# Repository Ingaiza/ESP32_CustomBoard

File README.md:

# Custom ESP32-C3 Development Board

## Overview
This repository contains the KiCad PCB design files for a custom development board powered by the ESP32-C3 microcontroller. This board integrates essential environmental sensing, audio input, and power management features. It serves as a robust hardware foundation for developing advanced embedded systems and IoT devices.

## Hardware Features

* **Microcontroller**: Powered by the ESP32-C3-WROOM-02-H4 module, offering Wi-Fi and Bluetooth LE connectivity.
* **Power Management**: 
    * Modern USB-C connector interface.
    * Onboard 3.3V voltage regulation via the LM1117MPX-3.3 LDO.
    * Integrated LiPo battery charging circuit utilizing the MCP73871 IC.
* **USB-to-UART Interface**: Features the CP2102N bridge for reliable serial communication and seamless flashing.
* **Memory & Storage**:
    * External 32Mb (4MB) W25Q32JVSSIQ Flash memory.
    * Dedicated MicroSD card circuit for extensive data logging.
* **Integrated Sensors**:
    * **BME280**: Environmental sensor for capturing temperature, humidity, and barometric pressure data.
    * **TEMT6000**: Ambient light sensor for environmental illumination tracking.
    * **Audio**: Electret microphone (CMC-5042PF-AC) paired with a MAX4466EXK operational amplifier for high-quality audio input.
* **User Interface & Expansion**:
    * Auto-program circuitry equipped with standard Boot and Reset tactile buttons.
    * Dedicated I2C connector optimized for OLED displays.
    * Accessible remaining GPIO breakout headers for rapid prototyping.

## Visuals & Documentation

### Top View

### Bottom View Routing

### Schematic
The complete circuit design can be viewed here: [Schematic PDF](media/Shematic.pdf)

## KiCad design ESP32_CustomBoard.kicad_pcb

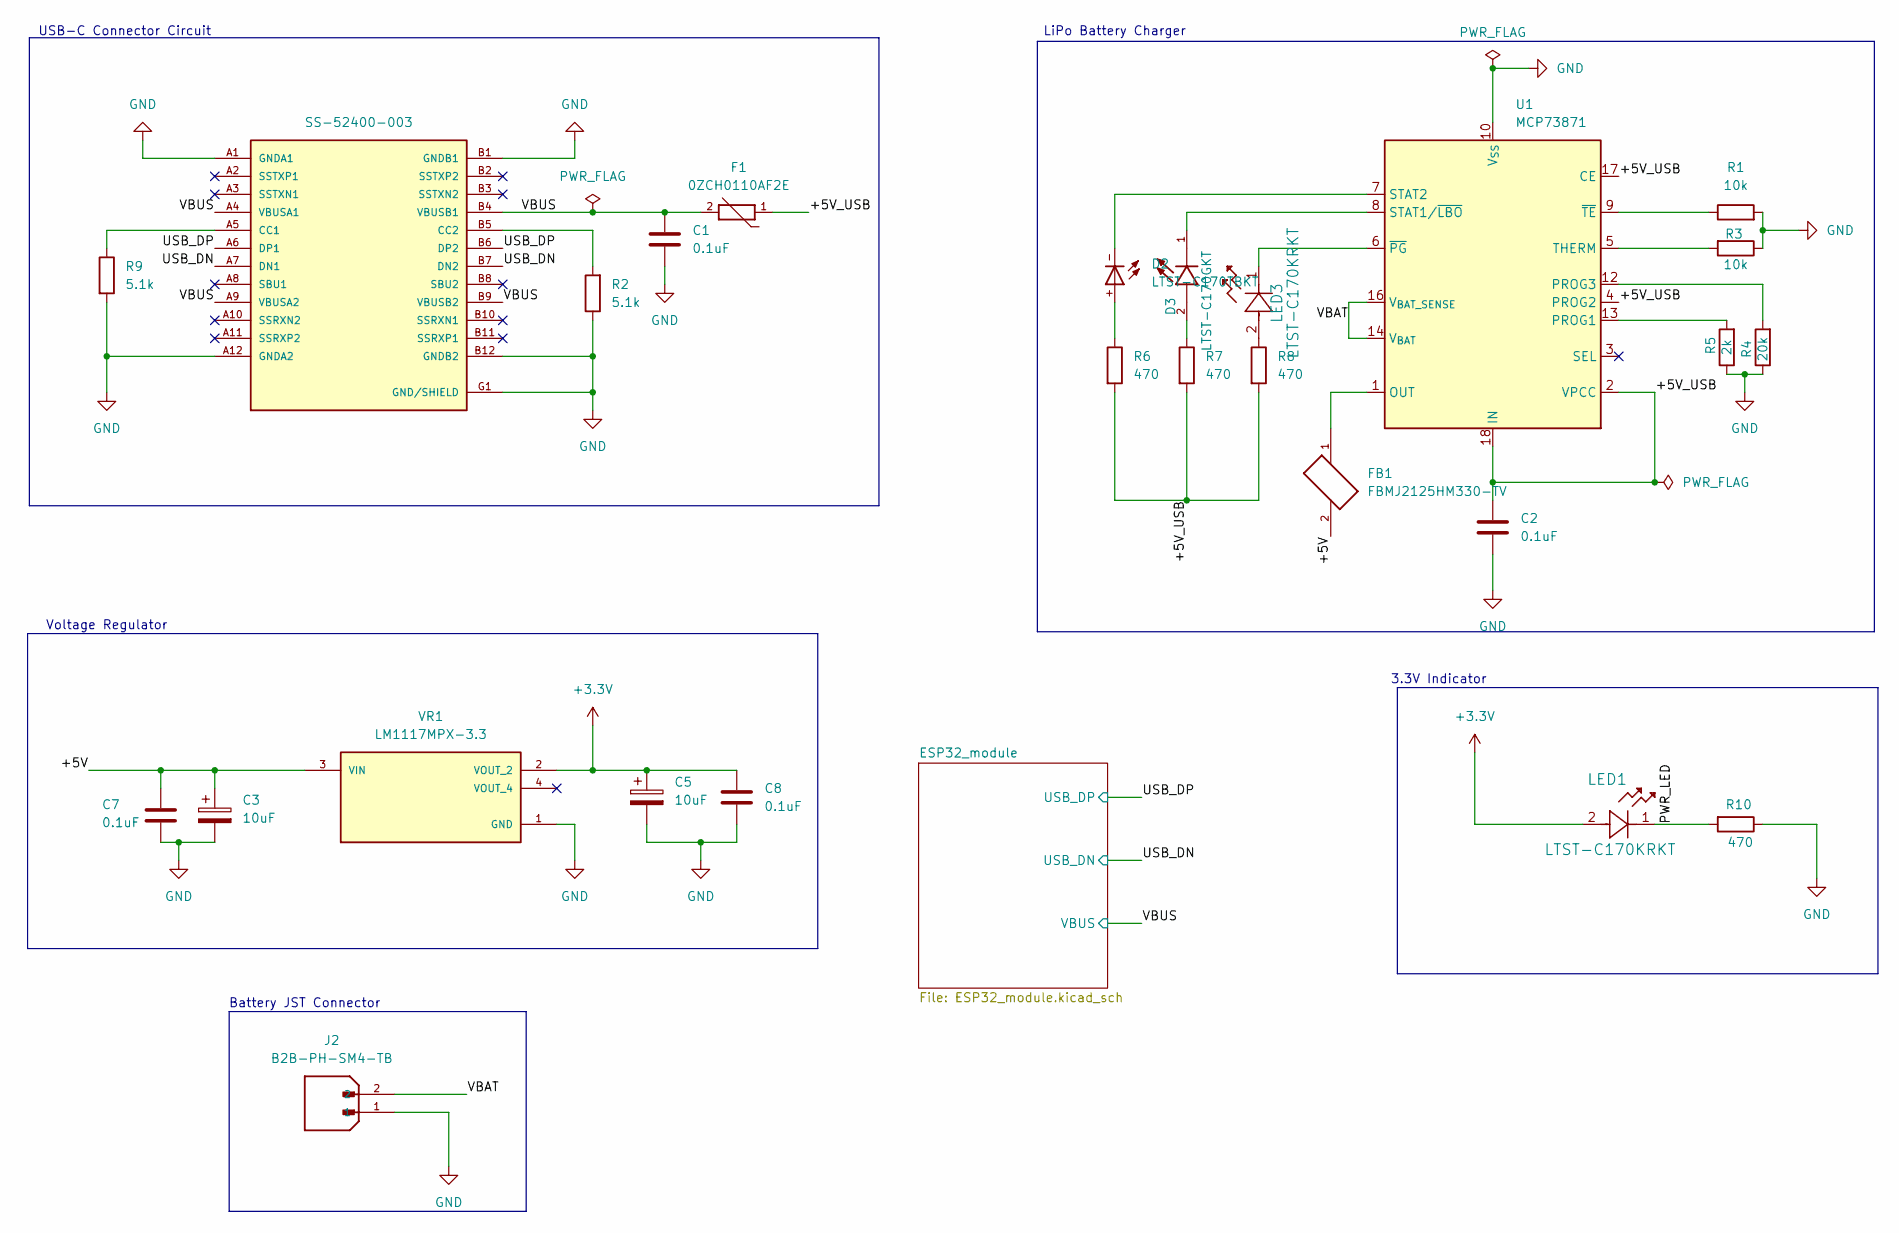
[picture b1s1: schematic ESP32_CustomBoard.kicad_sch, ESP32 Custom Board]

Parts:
C1, C2, C7, C8: 0.1uF; C_0805_2012Metric
C3, C5: 10uF; RESC3216X125N
D2: LTST-C170TBKT; DIOC200X125X110
D3: LTST-C170GKT; LED_LTST-C170GKT; PARTREV I
F1: 0ZCH0110AF2E; FUSC3225X100N; PARTREV Apr2023
FB1: FBMJ2125HM330-TV; BEADC2012X105N
J1: SS-52400-003; BELFUSE_SS-52400-003; PARTREV A0
J2: B2B-PH-SM4-TB; JST_B2B-PH-SM4-TB; PARTREV N/A
LED1, LED3: LTST-C170KRKT; LED_LTST-C170KRKT_LTO
R1, R3: 10k; R_0805_2012Metric
R2, R9: 5.1k; R_0805_2012Metric
R4: 20k; R_0805_2012Metric
R5: 2k; R_0805_2012Metric
R6, R7, R8, R10: 470; R_0805_2012Metric
U1: MCP73871; QFN-20-1EP_4x4mm_P0.5mm_EP2.5x2.5mm
VR1: LM1117MPX-3.3; VREG_LM1117MPX-3.3; PARTREV O

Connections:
+3.3V: C5.1, C8.1, LED1.2, VR1.2 (VOUT_2); also elsewhere on the board
/+5V: C3.1, C7.1, FB1.2, VR1.3 (VIN)
/+5V_USB: C2.1, F1.1, R6.2, R7.2, R8.2, U1.2 (VPCC), U1.4 (PROG2), U1.17 (CE), U1.18 (IN), U1.19 (IN)
/PWR_LED: LED1.1, R10.2
/USB_DN: J1.A7 (DN1), J1.B7 (DN2); also elsewhere on the board
/USB_DP: J1.A6 (DP1), J1.B6 (DP2); also elsewhere on the board
/VBAT: J2.2, U1.14 (V_{BAT}), U1.15 (V_{BAT}), U1.16 (V_{BAT_SENSE})
/VBUS: C1.1, F1.2, J1.A4 (VBUSA1), J1.A9 (VBUSA2), J1.B4 (VBUSB1), J1.B9 (VBUSB2); also elsewhere on the board
GND: C1.2, C2.2, C3.2, C5.2, C7.2, C8.2, J1.A1 (GNDA1), J1.A12 (GNDA2), J1.B1 (GNDB1), J1.B12 (GNDB2), J1.G1 (GND/SHIELD), J1.G2 (GND/SHIELD), J1.G3 (GND/SHIELD), J1.G4 (GND/SHIELD), J1.S1 (GND/SHIELD), J1.S2 (GND/SHIELD), J1.S3 (GND/SHIELD), J1.S4 (GND/SHIELD), J2.1, R1.2, R2.1, R3.1, R4.1, R5.1, R9.2, R10.1, U1.10 (V_{SS}), U1.11 (V_{SS}), U1.21 (V_{SS}), VR1.1 (GND); also elsewhere on the board
unnamed: D2.+, R6.1
unnamed: D3.2, R7.1
unnamed: FB1.1, U1.1 (OUT), U1.20 (OUT)
unnamed: J1.A5 (CC1), R9.1
unnamed: J1.B5 (CC2), R2.2
unnamed: LED3.2, R8.1
unnamed: R5.2, U1.13 (PROG1)
unnamed: R4.2, U1.12 (PROG3)
unnamed: D3.1, U1.8 (STAT1/~LBO)
unnamed: D2.-, U1.7 (STAT2)
unnamed: R3.2, U1.5 (THERM)
unnamed: LED3.1, U1.6 (~PG)
unnamed: R1.1, U1.9 (~TE)

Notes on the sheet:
USB-C Connector Circuit
Voltage Regulator
LiPo Battery Charger
Battery JST Connector
3.3V Indicator

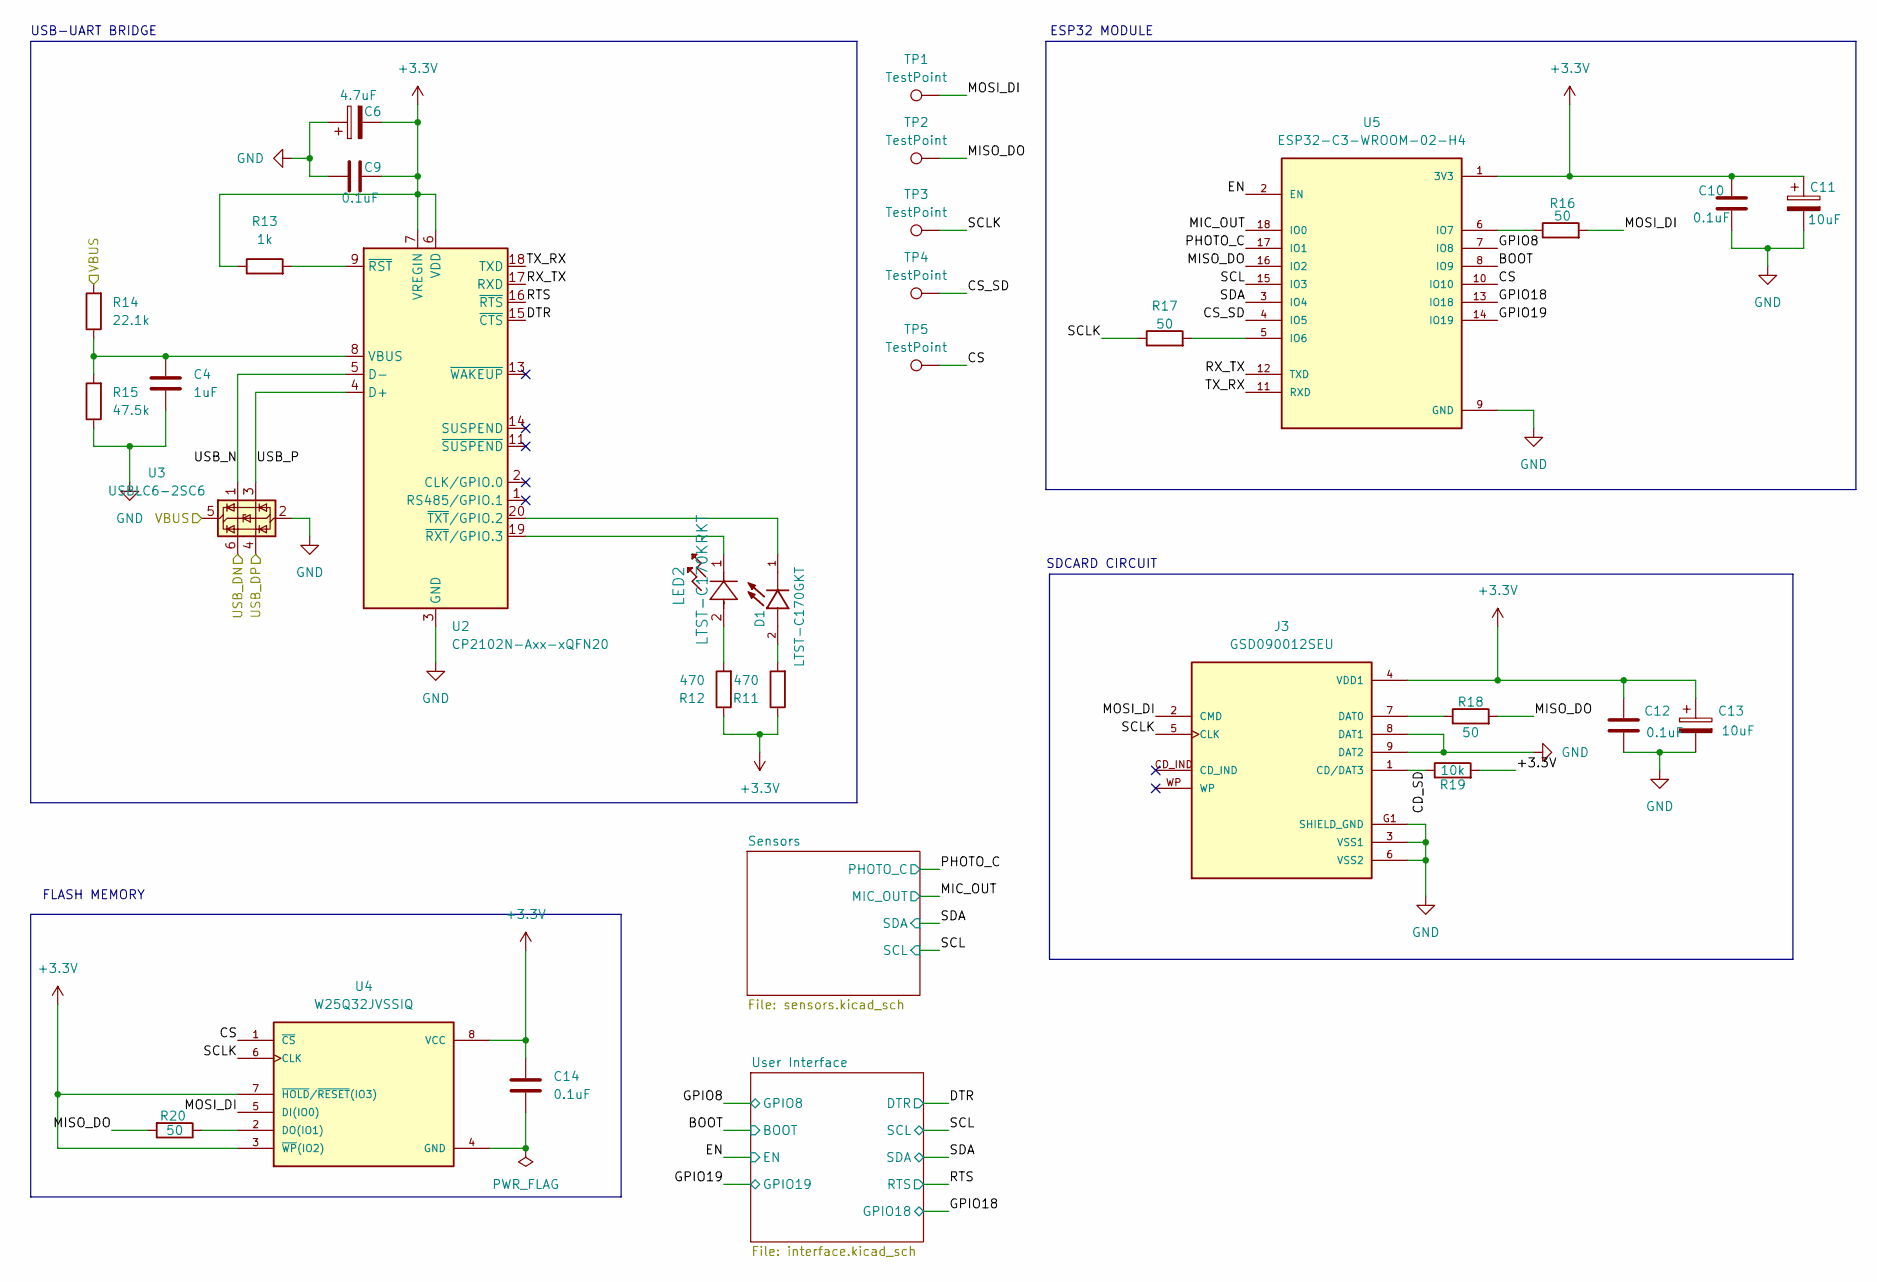
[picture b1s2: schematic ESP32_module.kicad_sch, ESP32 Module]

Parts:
C4: 1uF; C_0805_2012Metric
C6: 4.7uF; RESC3216X125N
C9, C10, C12, C14: 0.1uF; C_0805_2012Metric
C11, C13: 10uF; RESC3216X125N
D1: LTST-C170GKT; LED_LTST-C170GKT; PARTREV I
J3: GSD090012SEU; AMPHENOL_GSD090012SEU; PARTREV E
LED2: LTST-C170KRKT; LED_LTST-C170KRKT_LTO
R11, R12: 470; R_0805_2012Metric
R13: 1k; R_0805_2012Metric
R14: 22.1k; R_0805_2012Metric
R15: 47.5k; R_0805_2012Metric
R16, R17, R18, R20: 50; R_0805_2012Metric
R19: 10k; R_0805_2012Metric
TP1, TP2, TP3, TP4, TP5: TestPoint; TestPoint_Pad_D1.0mm
U2: CP2102N-Axx-xQFN20; SiliconLabs_QFN-20-1EP_3x3mm_P0.5mm_EP1.8x1.8mm
U3: USBLC6-2SC6; SOT-23-6
U4: W25Q32JVSSIQ; SOIC127P790X216-8N; M_PART_NUMBER W25QXX
U5: ESP32-C3-WROOM-02-H4; MODULE_ESP32-C3-WROOM-02-H4

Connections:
+3.3V: C6.2, C9.2, C10.2, C11.1, C12.1, C13.1, C14.1, J3.4 (VDD1), R11.1, R12.1, R13.1, R19.2, U2.6 (VDD), U2.7 (VREGIN), U4.3 (~WP(IO2)), U4.7 (~HOLD/~RESET(IO3)), U4.8 (VCC), U5.1 (3V3); also elsewhere on the board
/ESP32_module/BOOT: U5.8 (IO9); also elsewhere on the board
/ESP32_module/CD_SD: J3.1 (CD/DAT3), R19.1
/ESP32_module/CS: TP5.1, U4.1 (~CS), U5.10 (IO10)
/ESP32_module/CS_SD: TP4.1, U5.4 (IO5)
/ESP32_module/DTR: U2.15 (~CTS); also elsewhere on the board
/ESP32_module/EN: U5.2 (EN); also elsewhere on the board
/ESP32_module/GPIO8: U5.7 (IO8); also elsewhere on the board
/ESP32_module/GPIO18: U5.13 (IO18); also elsewhere on the board
/ESP32_module/GPIO19: U5.14 (IO19); also elsewhere on the board
/ESP32_module/MIC_OUT: U5.18 (IO0); also elsewhere on the board
/ESP32_module/MISO_DO: R18.2, R20.2, TP2.1, U5.16 (IO2)
/ESP32_module/MOSI_DI: J3.2 (CMD), R16.2, TP1.1, U4.5 (DI(IO0))
/ESP32_module/PHOTO_C: U5.17 (IO1); also elsewhere on the board
/ESP32_module/RTS: U2.16 (~RTS); also elsewhere on the board
/ESP32_module/RX_TX: U2.17 (RXD), U5.12 (TXD)
/ESP32_module/SCL: U5.15 (IO3); also elsewhere on the board
/ESP32_module/SCLK: J3.5 (CLK), R17.1, TP3.1, U4.6 (CLK)
/ESP32_module/SDA: U5.3 (IO4); also elsewhere on the board
/ESP32_module/TX_RX: U2.18 (TXD), U5.11 (RXD)
/ESP32_module/USB_N: U2.5 (D-), U3.1 (I/O1)
/ESP32_module/USB_P: U2.4 (D+), U3.3 (I/O2)
/USB_DN: U3.6 (I/O1); also elsewhere on the board
/USB_DP: U3.4 (I/O2); also elsewhere on the board
/VBUS: R14.2, U3.5 (VBUS); also elsewhere on the board
GND: C4.2, C6.1, C9.1, C10.1, C11.2, C12.2, C13.2, J3.3 (VSS1), J3.6 (VSS2), J3.8 (DAT1), J3.9 (DAT2), J3.G1 (SHIELD_GND), J3.G2 (SHIELD_GND), J3.G3 (SHIELD_GND), J3.G4 (SHIELD_GND), R15.1, U2.3 (GND), U2.12 (GND), U2.21 (GND), U3.2 (GND), U5.9 (GND), U5.19 (GND), U5.20 (GND), U5.21 (GND), U5.22 (GND), U5.23 (GND), U5.24 (GND), U5.25 (GND), U5.26 (GND), U5.27 (GND), U5.28 (GND), U5.29 (GND), U5.30 (GND), U5.31 (GND), U5.32 (GND), U5.33 (GND), U5.34 (GND), U5.35 (GND), U5.36 (GND), U5.37 (GND), U5.38 (GND), U5.39 (GND); also elsewhere on the board
unnamed: D1.2, R11.2
unnamed: J3.7 (DAT0), R18.1
unnamed: LED2.2, R12.2
unnamed: C4.1, R14.1, R15.2, U2.8 (VBUS)
unnamed: R13.2, U2.9 (~RST)
unnamed: LED2.1, U2.19 (~RXT/GPIO.3)
unnamed: D1.1, U2.20 (~TXT/GPIO.2)
unnamed: R20.1, U4.2 (DO(IO1))
unnamed: C14.2, U4.4 (GND)
unnamed: R17.2, U5.5 (IO6)
unnamed: R16.1, U5.6 (IO7)

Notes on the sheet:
SDCARD CIRCUIT
ESP32 MODULE
USB-UART BRIDGE
FLASH MEMORY

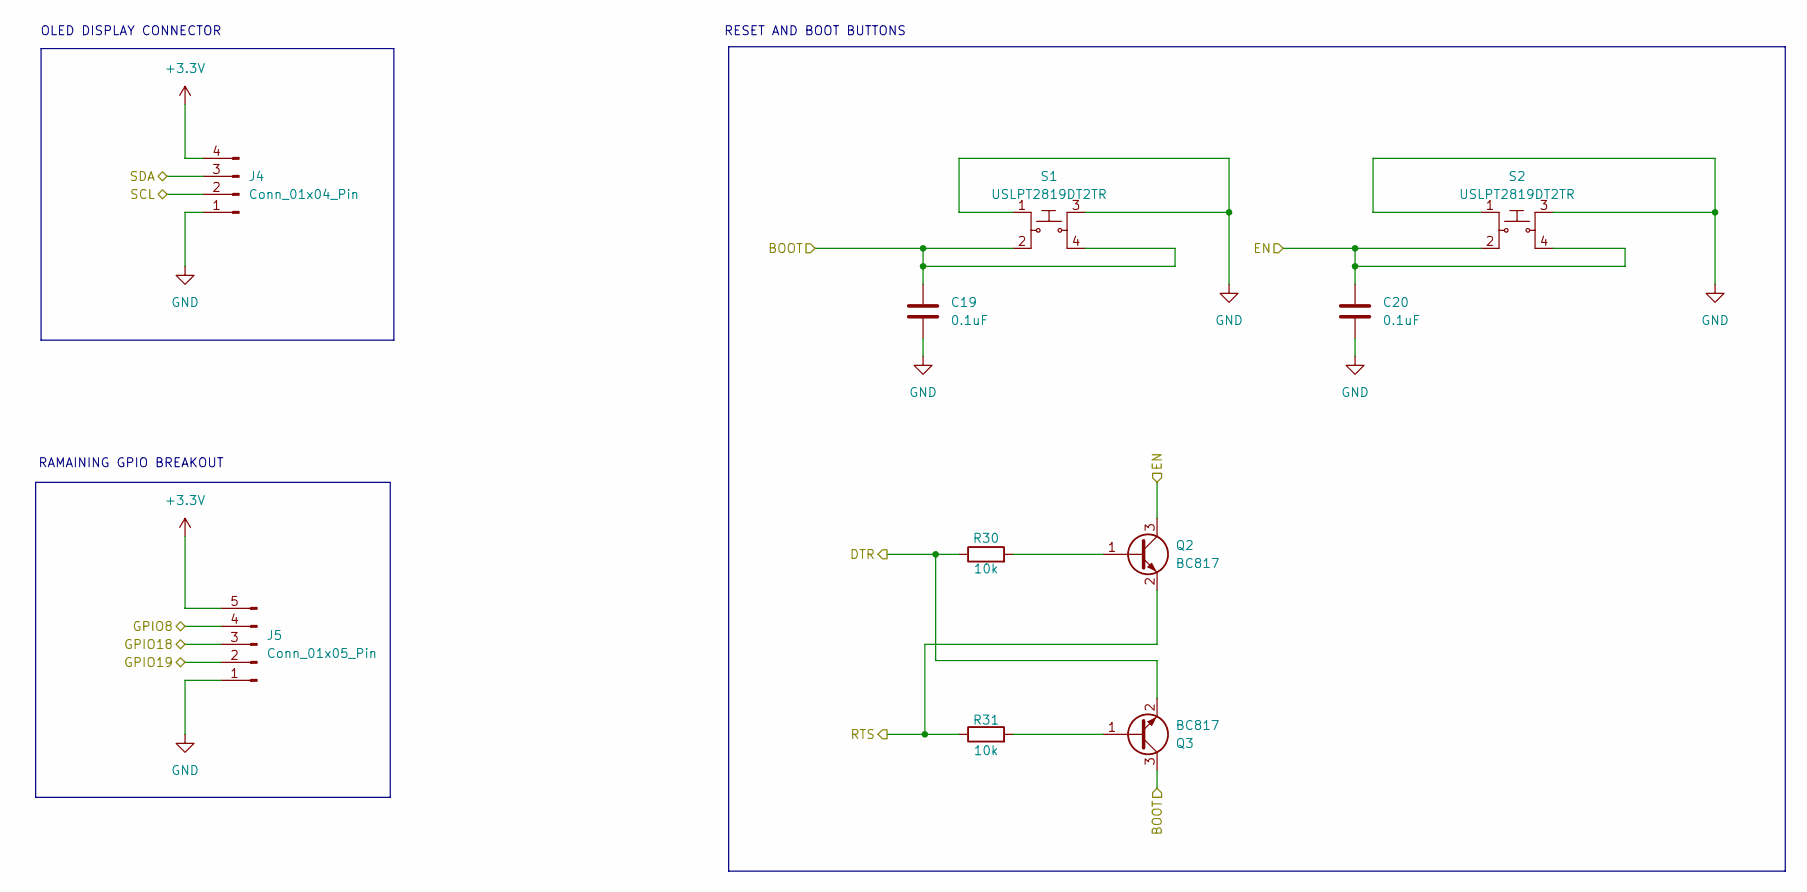
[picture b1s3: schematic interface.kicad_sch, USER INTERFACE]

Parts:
C19, C20: 0.1uF; C_0805_2012Metric
J4: Conn_01x04_Pin; PinHeader_1x04_P2.54mm_Vertical
J5: Conn_01x05_Pin; PinHeader_1x05_P2.54mm_Vertical
Q2, Q3: BC817; SOT-23
R30, R31: 10k; R_0805_2012Metric
S1, S2: USLPT2819DT2TR; SW_USLPT2819DT2TR; PARTREV P; Digi-Key_PN EG4621CT-ND

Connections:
+3.3V: J4.4, J5.5; also elsewhere on the board
/ESP32_module/BOOT: C19.1, Q3.3 (C), S1.2, S1.4; also elsewhere on the board
/ESP32_module/DTR: Q3.2 (E), R30.1; also elsewhere on the board
/ESP32_module/EN: C20.1, Q2.3 (C), S2.2, S2.4; also elsewhere on the board
/ESP32_module/GPIO8: J5.4; also elsewhere on the board
/ESP32_module/GPIO18: J5.3; also elsewhere on the board
/ESP32_module/GPIO19: J5.2; also elsewhere on the board
/ESP32_module/RTS: Q2.2 (E), R31.1; also elsewhere on the board
/ESP32_module/SCL: J4.2; also elsewhere on the board
/ESP32_module/SDA: J4.3; also elsewhere on the board
GND: C19.2, C20.2, J4.1, J5.1, S1.1, S1.3, S2.1, S2.3; also elsewhere on the board
unnamed: Q2.1 (B), R30.2
unnamed: Q3.1 (B), R31.2

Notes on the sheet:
OLED DISPLAY CONNECTOR
RESET AND BOOT BUTTONS
RAMAINING GPIO BREAKOUT

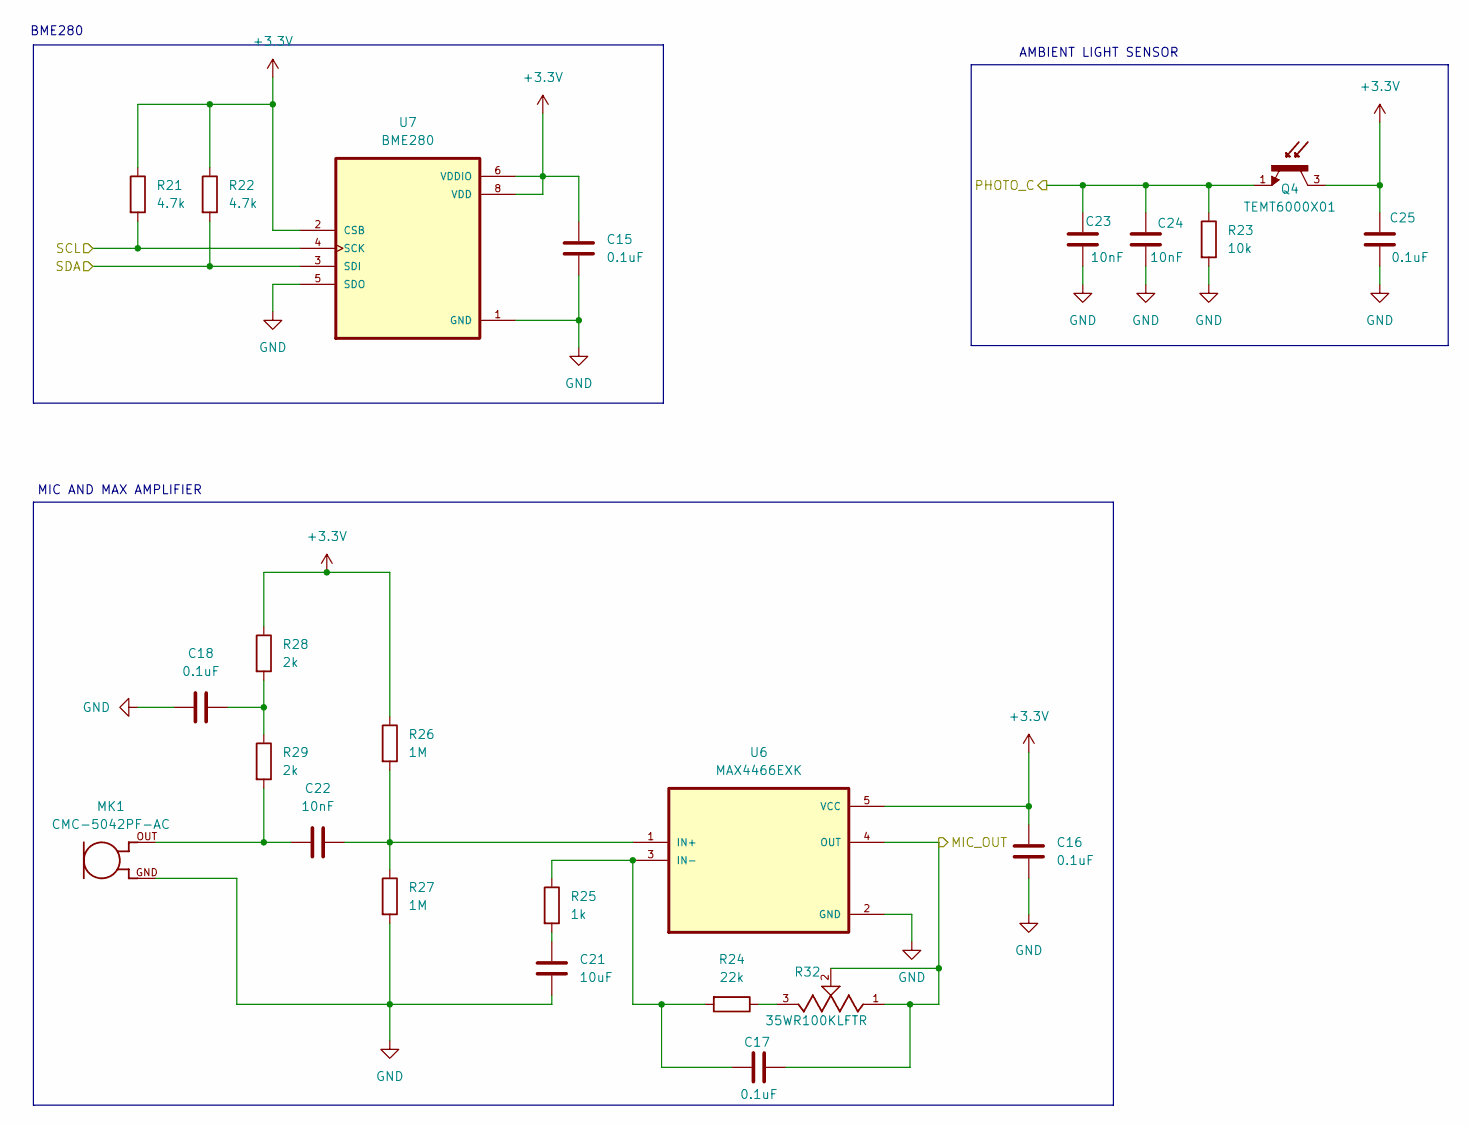
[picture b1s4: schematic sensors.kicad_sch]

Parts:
C15, C16, C17, C18, C25: 0.1uF; C_0805_2012Metric
C21: 10uF; C_0805_2012Metric
C22, C23, C24: 10nF; C_0805_2012Metric
MK1: CMC-5042PF-AC; CUI_CMC-5042PF-AC
Q4: TEMT6000X01; TRANS_TEMT6000X01; PARTREV 1.9
R21, R22: 4.7k; R_0805_2012Metric
R23: 10k; R_0805_2012Metric
R24: 22k; R_0805_2012Metric
R25: 1k; R_0805_2012Metric
R26, R27: 1M; R_0805_2012Metric
R28, R29: 2k; R_0805_2012Metric
R32: 35WR100KLFTR; TRIM_35WR100KLFTR; PARTREV D
U6: MAX4466EXK; SOT65P210X110-5N
U7: BME280; PSON65P250X250X100-8N

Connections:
+3.3V: C15.1, C16.1, C25.1, Q4.3, R21.1, R22.1, R26.1, R28.1, U6.5 (VCC), U7.2 (CSB), U7.6 (VDDIO), U7.8 (VDD); also elsewhere on the board
/ESP32_module/MIC_OUT: C17.2, R32.1, R32.2, U6.4 (OUT); also elsewhere on the board
/ESP32_module/PHOTO_C: C23.1, C24.1, Q4.1, R23.1; also elsewhere on the board
/ESP32_module/SCL: R21.2, U7.4 (SCK); also elsewhere on the board
/ESP32_module/SDA: R22.2, U7.3 (SDI); also elsewhere on the board
GND: C15.2, C16.2, C18.1, C21.2, C23.2, C24.2, C25.2, MK1.GND, R23.2, R27.2, U6.2 (GND), U7.1 (GND), U7.5 (SDO), U7.7 (GND); also elsewhere on the board
unnamed: C18.2, R28.2, R29.1
unnamed: C21.1, R25.2
unnamed: C22.1, MK1.OUT, R29.2
unnamed: R24.1, R32.3
unnamed: C22.2, R26.2, R27.1, U6.1 (IN+)
unnamed: C17.1, R24.2, R25.1, U6.3 (IN-)

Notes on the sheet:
AMBIENT LIGHT SENSOR
BME280
MIC AND MAX AMPLIFIER

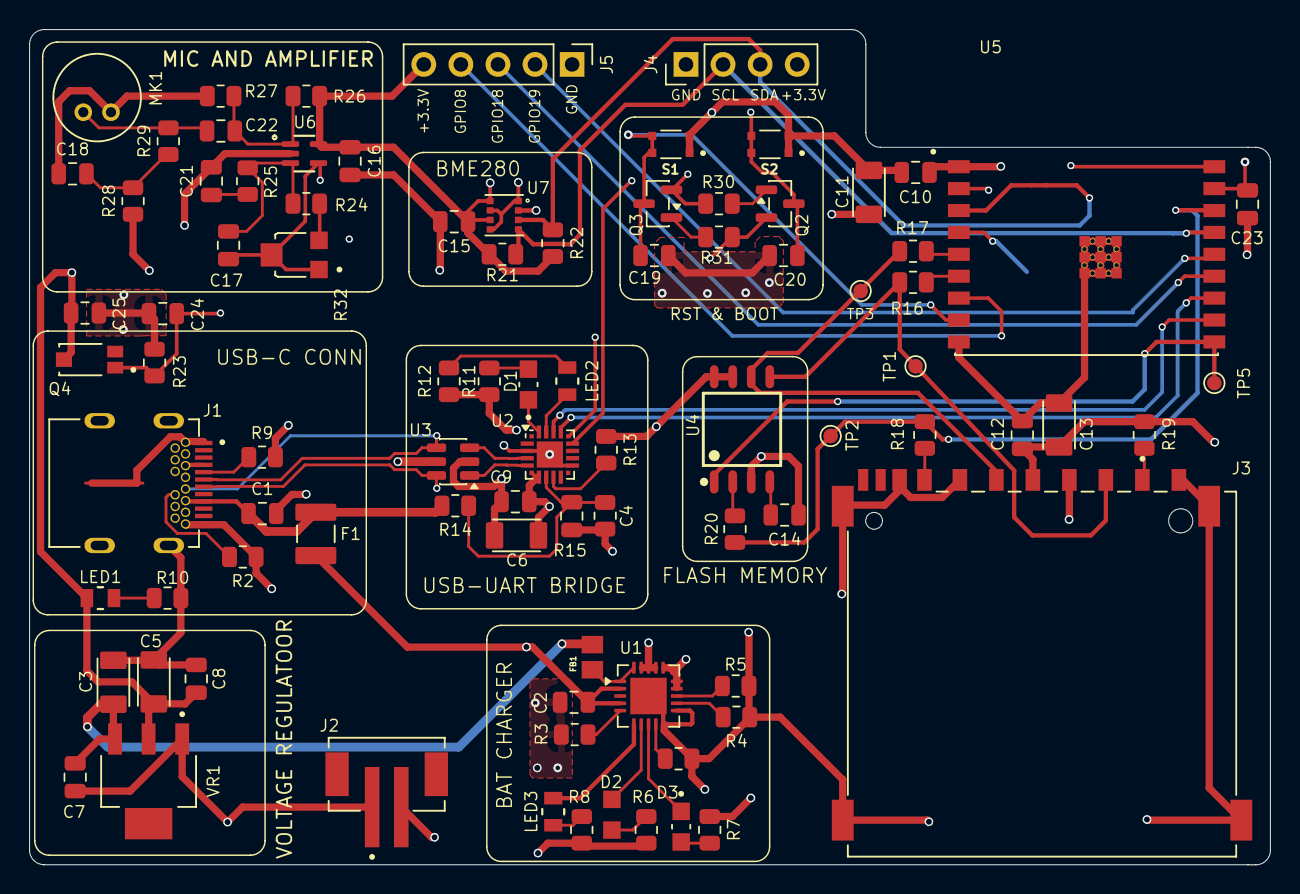
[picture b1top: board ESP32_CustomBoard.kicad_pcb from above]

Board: 4 copper layers, 85.0 x 57.2 mm, 89 parts (1 on the bottom side), 62 nets.

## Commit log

2026-02-23 Completed Sheet 1 - Power Supply
2026-02-23 Completed Sheet 2- ESP32 Module
2026-02-23 Completed Sheet 3- Sensors and Sheet 4- User Interface
2026-02-24 Completed Schematic Layout
2026-02-24 Net Class Assignment. Created Power, USB_Comms,UART, SPI, I2C, Sensors and CMD Net Classes and assigned nets
2026-02-25 Fixed Audio Amp Circuit
2026-02-25 Fixed the Footprint assignment nonsense
2026-02-25 Fixed ONE MORE Footprint misassignment
2026-02-26 Layout Placement
2026-02-27 Power copper zones and Placement complete
2026-02-27 Completed Routing
2026-02-27 3D models added
2026-03-10 fixed errors, completed silkscreen and 3D assignment
2026-03-10 Schematic Fixes
2026-03-11 Completed layout fix
2026-03-11 created media dir
2026-03-11 minor
2026-03-11 Added README
2026-03-11 fixed README
2026-03-11 Fixed MIC silkscreen and updated media images
